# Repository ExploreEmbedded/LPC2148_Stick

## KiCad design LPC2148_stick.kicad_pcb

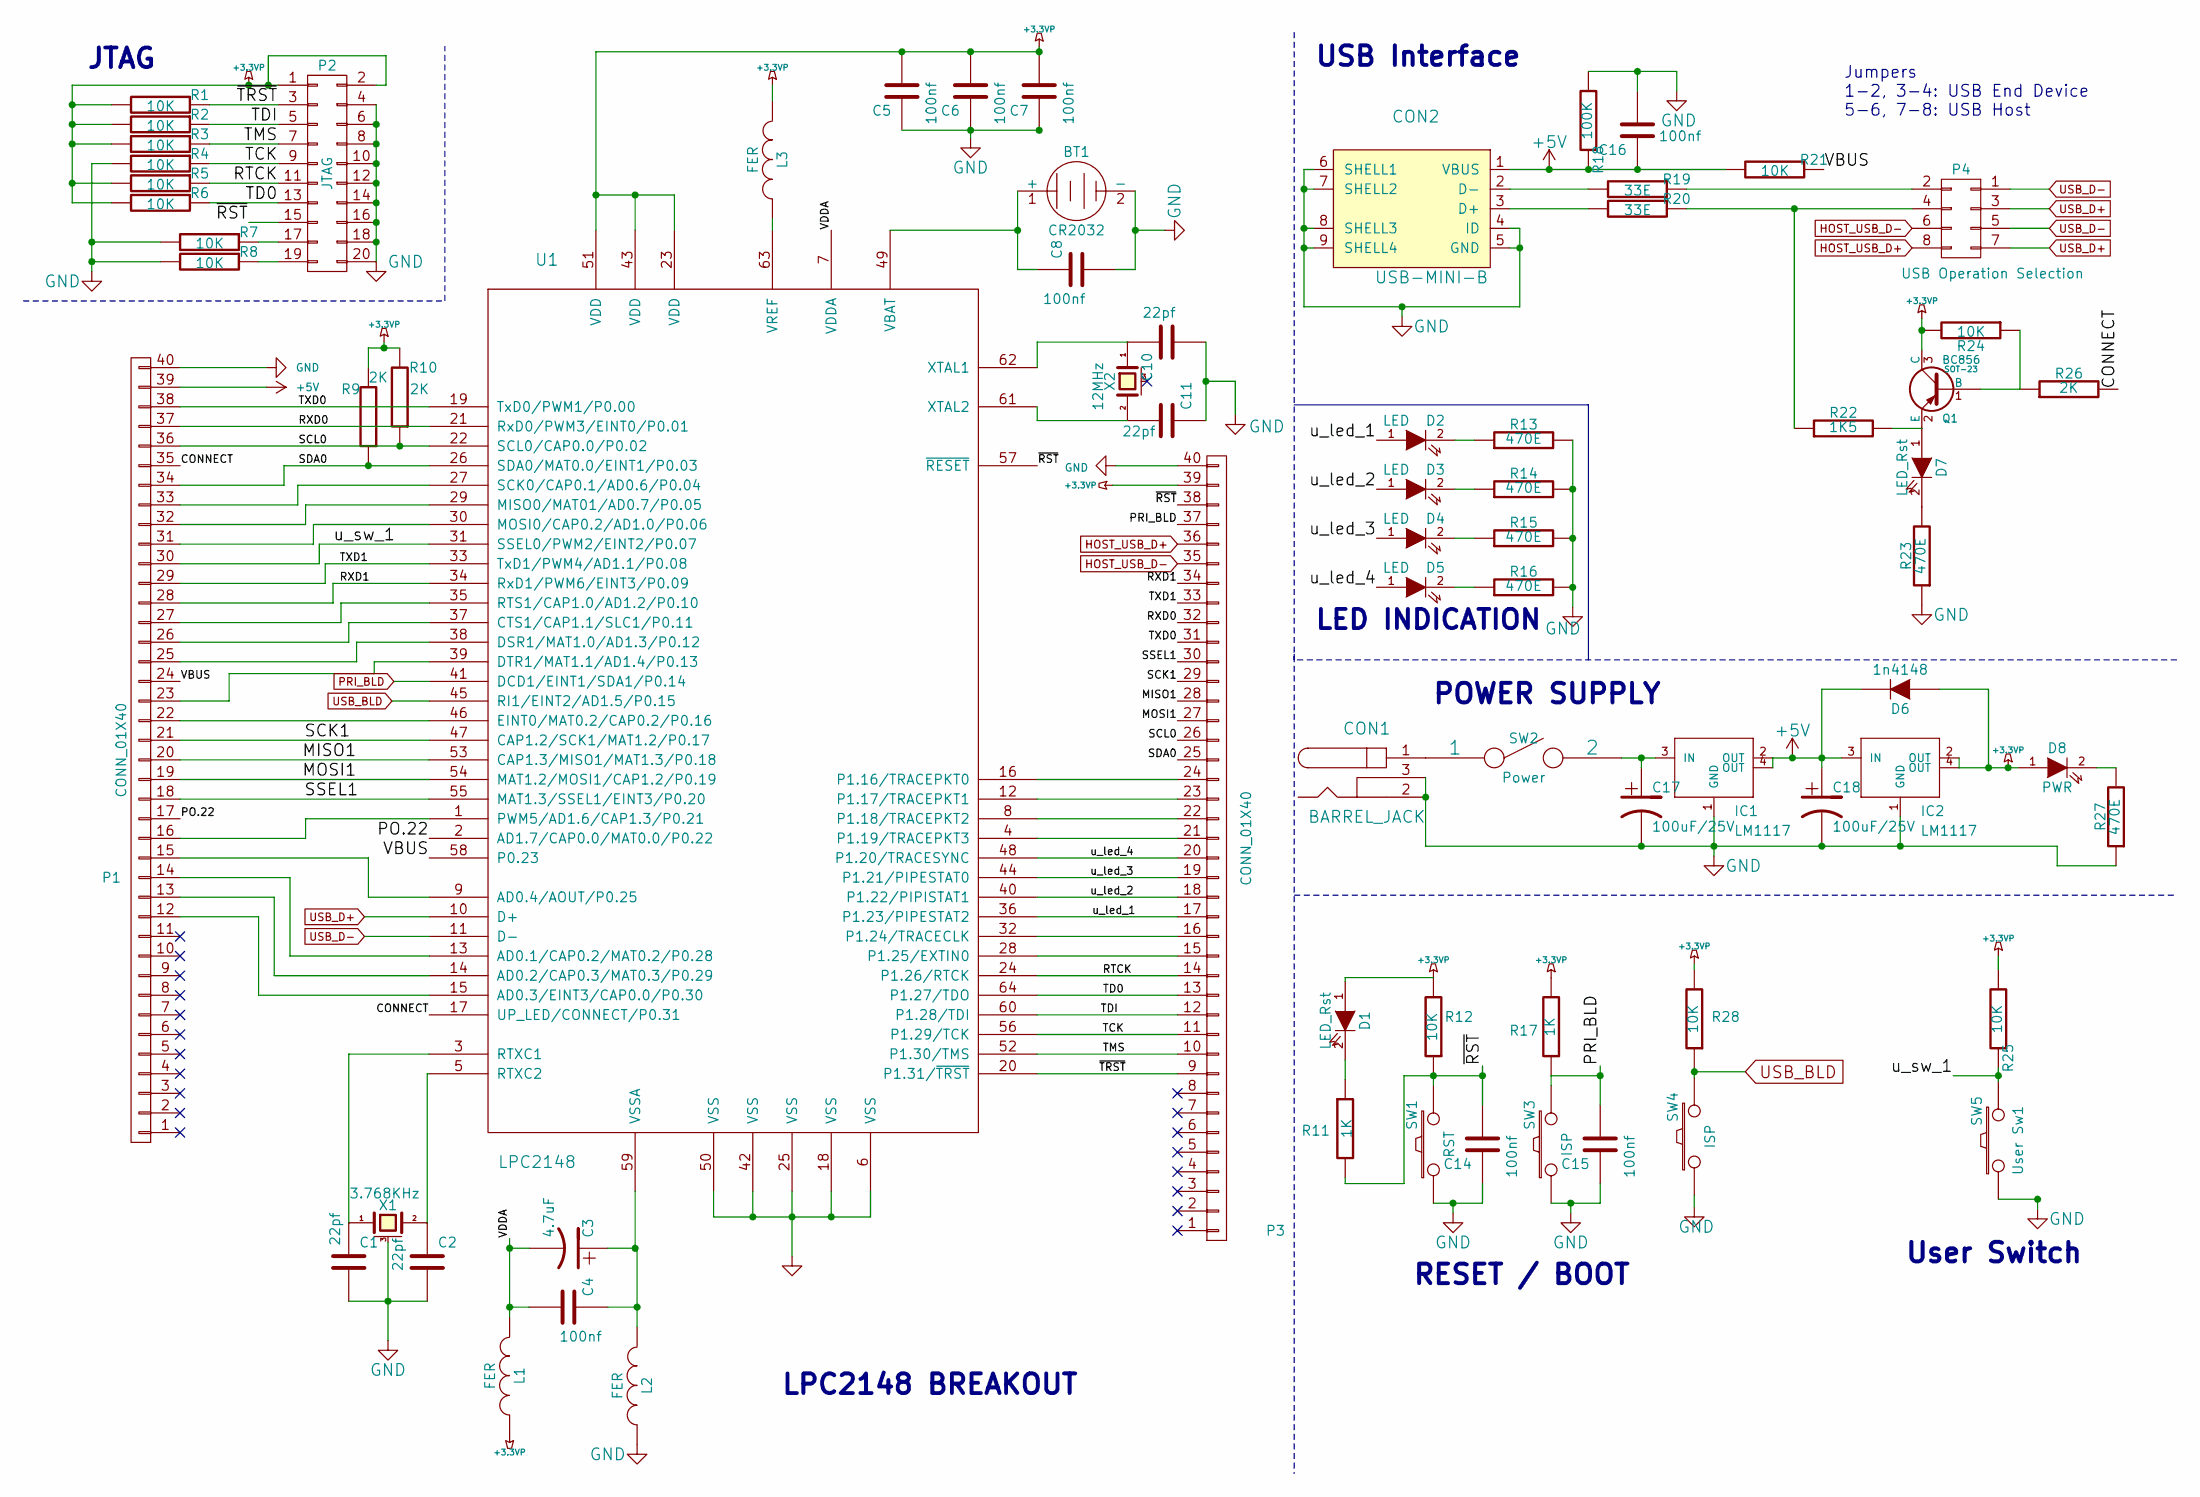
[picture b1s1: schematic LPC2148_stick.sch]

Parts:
BT1: CR2032
C1, C2, C10, C11: 22pf
C3: 4.7uF
C4, C5, C6, C7, C8, C14, C15, C16: 100nf
C17, C18: 100uF/25V
CON1: BARREL_JACK
CON2: USB-MINI-B
D1, D7: LED_Rst
D2, D3, D4, D5: LED
D6: 1n4148
D8: PWR
IC1, IC2: LM1117
L1, L2, L3: FER
P1, P3: CONN_01X40
P2: JTAG
P4: USB Operation Selection
Q1: BC856; SOT-23
R1, R2, R3, R4, R5, R6, R7, R8, R12, R21, R24, R25, R28: 10K
R9, R10, R26: 2K
R11, R17: 1K
R13, R14, R15, R16, R23, R27: 470E
R18: 100K
R19, R20: 33E
R22: 1K5
SW1: RST
SW2: Power
SW3, SW4: ISP
SW5: User Sw1
U1: LPC2148
X1: 3.768KHz
X2: 12MHz

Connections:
+3.3VP: C5.2, C6.2, C7.2, D1.1 (A), D6.1 (A), D8.1 (A), IC2.2 (OUT), IC2.4 (OUT), L1.2, L3.1, P2.1, P2.2, P3.39, Q1.3 (C), R1.2, R2.2, R3.2, R5.2, R6.2, R9.2, R10.2, R12.2, R17.2, R24.2, R25.2, R28.2, U1.23 (VDD), U1.43 (VDD), U1.51 (VDD)
+5V: C16.1, C18.1, CON2.1 (VBUS), D6.2 (K), IC1.2 (OUT), IC1.4 (OUT), IC2.3 (IN), P1.39, R18.1, R21.2
/CONNECT: P1.35, R26.2, U1.17 (UP_LED/CONNECT/P0.31)
/MISO1: P1.20, P3.28, U1.53 (CAP1.3/MISO1/MAT1.3/P0.18)
/MOSI1: P1.19, P3.27, U1.54 (MAT1.2/MOSI1/CAP1.2/P0.19)
/RTCK: P2.11, P3.14, R5.1, U1.24 (P1.26/RTCK)
/RXD0: P1.37, P3.32, U1.21 (RxD0/PWM3/EINT0/P0.01)
/RXD1: P1.28, P3.34, U1.34 (RxD1/PWM6/EINT3/P0.09)
/SCK1: P1.21, P3.29, U1.47 (CAP1.2/SCK1/MAT1.2/P0.17)
/SCL0: P1.36, P3.26, R10.1, U1.22 (SCL0/CAP0.0/P0.02)
/SDA0: P1.34, P3.25, R9.1, U1.26 (SDA0/MAT0.0/EINT1/P0.03)
/SSEL1: P1.18, P3.30, U1.55 (MAT1.3/SSEL1/EINT3/P0.20)
/TCK: P2.9, P3.11, R4.1, U1.56 (P1.29/TCK)
/TD0: P2.13, P3.13, R6.1, U1.64 (P1.27/TDO)
/TDI: P2.5, P3.12, R2.1, U1.60 (P1.28/TDI)
/TMS: P2.7, P3.10, R3.1, U1.52 (P1.30/TMS)
/TXD0: P1.38, P3.31, U1.19 (TxD0/PWM1/P0.00)
/TXD1: P1.29, P3.33, U1.33 (TxD1/PWM4/AD1.1/P0.08)
/VBUS: P1.24, R21.1, U1.58 (P0.23)
/VDDA: C3.2, C4.2, L1.1, U1.7 (VDDA)
/u_led_1: D2.1 (A), P3.17, U1.36 (P1.23/PIPESTAT2)
/u_led_2: D3.1 (A), P3.18, U1.40 (P1.22/PIPISTAT1)
/u_led_3: D4.1 (A), P3.19, U1.44 (P1.21/PIPESTAT0)
/u_led_4: D5.1 (A), P3.20, U1.48 (P1.20/TRACESYNC)
/u_sw_1: P1.30, R25.1, SW5.2, U1.31 (SSEL0/PWM2/EINT2/P0.07)
/~RST: C14.2, P2.15, P3.38, R11.2, R12.1, SW1.2, U1.57 (~RESET)
/~TRST: P2.3, P3.9, R1.1, U1.20 (P1.31/~TRST)
GND: BT1.2 (-), C1.2, C2.2, C5.1, C6.1, C7.1, C8.2, C10.2, C11.1, C14.1, C15.1, C16.2, C17.2, C18.2, CON1.2, CON1.3, CON2.4 (ID), CON2.5 (GND), CON2.6 (SHELL1), CON2.7 (SHELL2), CON2.8 (SHELL3), CON2.9 (SHELL4), IC1.1 (GND), IC2.1 (GND), L2.2, P1.40, P2.4, P2.6, P2.8, P2.10, P2.12, P2.14, P2.16, P2.18, P2.20, P3.40, R4.2, R7.2, R8.2, R13.2, R14.2, R15.2, R16.2, R18.2, R23.1, R27.1, SW1.1, SW3.1, SW4.1, SW5.1, U1.6 (VSS), U1.18 (VSS), U1.25 (VSS), U1.42 (VSS), U1.50 (VSS), X1.3 (case)
HOST_USB_D+: P3.36, P4.8
HOST_USB_D-: P3.35, P4.6
unnamed: BT1.1 (+), C8.1, U1.49 (VBAT)
unnamed: C1.1, U1.3 (RTXC1), X1.1
unnamed: C2.1, U1.5 (RTXC2), X1.2
unnamed: C3.1, C4.1, L2.1, U1.59 (VSSA)
unnamed: C10.1, U1.62 (XTAL1), X2.1
unnamed: C11.2, U1.61 (XTAL2), X2.2
unnamed: C17.1, IC1.3 (IN), SW2.2
unnamed: CON1.1, SW2.1
unnamed: CON2.2 (D-), R19.2
unnamed: CON2.3 (D+), R20.2
unnamed: D1.2 (K), R11.1
unnamed: D2.2 (K), R13.1
unnamed: D3.2 (K), R14.1
unnamed: D4.2 (K), R15.1
unnamed: D5.2 (K), R16.1
unnamed: D7.1 (A), Q1.2 (E), R22.2
unnamed: D7.2 (K), R23.2
unnamed: D8.2 (K), R27.2
unnamed: L3.2, U1.63 (VREF)
unnamed: P1.12, U1.15 (AD0.3/EINT3/CAP0.0/P0.30)
unnamed: P1.13, U1.14 (AD0.2/CAP0.3/MAT0.3/P0.29)
unnamed: P1.14, U1.13 (AD0.1/CAP0.2/MAT0.2/P0.28)
unnamed: P1.15, U1.9 (AD0.4/AOUT/P0.25)
unnamed: P1.22, U1.46 (EINT0/MAT0.2/CAP0.2/P0.16)
unnamed: P1.23, U1.39 (DTR1/MAT1.1/AD1.4/P0.13)
unnamed: P1.25, U1.38 (DSR1/MAT1.0/AD1.3/P0.12)
unnamed: P1.26, U1.37 (CTS1/CAP1.1/SLC1/P0.11)
unnamed: P1.27, U1.35 (RTS1/CAP1.0/AD1.2/P0.10)
unnamed: P1.31, U1.30 (MOSI0/CAP0.2/AD1.0/P0.06)
unnamed: P1.32, U1.29 (MISO0/MAT01/AD0.7/P0.05)
unnamed: P1.33, U1.27 (SCK0/CAP0.1/AD0.6/P0.04)
unnamed: P2.17, R7.1
unnamed: P2.19, R8.1
unnamed: P3.15, U1.28 (P1.25/EXTIN0)
unnamed: P3.16, U1.32 (P1.24/TRACECLK)
unnamed: P3.21, U1.4 (P1.19/TRACEPKT3)
unnamed: P3.22, U1.8 (P1.18/TRACEPKT2)
unnamed: P3.23, U1.12 (P1.17/TRACEPKT1)
unnamed: P3.24, U1.16 (P1.16/TRACEPKT0)
unnamed: P4.2, R19.1
unnamed: P4.4, R20.1, R22.1
unnamed: Q1.1 (B), R24.1, R26.1
PRI_BLD: C15.2, P3.37, R17.1, SW3.2, U1.41 (DCD1/EINT1/SDA1/P0.14)
USB_BLD: R28.1, SW4.2, U1.45 (RI1/EINT2/AD1.5/P0.15)
USB_D+: P4.3, P4.7, U1.10 (D+)
USB_D-: P4.1, P4.5, U1.11 (D-)

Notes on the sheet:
Jumpers 1-2, 3-4: USB End Device 5-6, 7-8: USB Host
JTAG
RESET / BOOT
LPC2148 BREAKOUT
USB Interface
POWER SUPPLY
User Switch
LED INDICATION

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
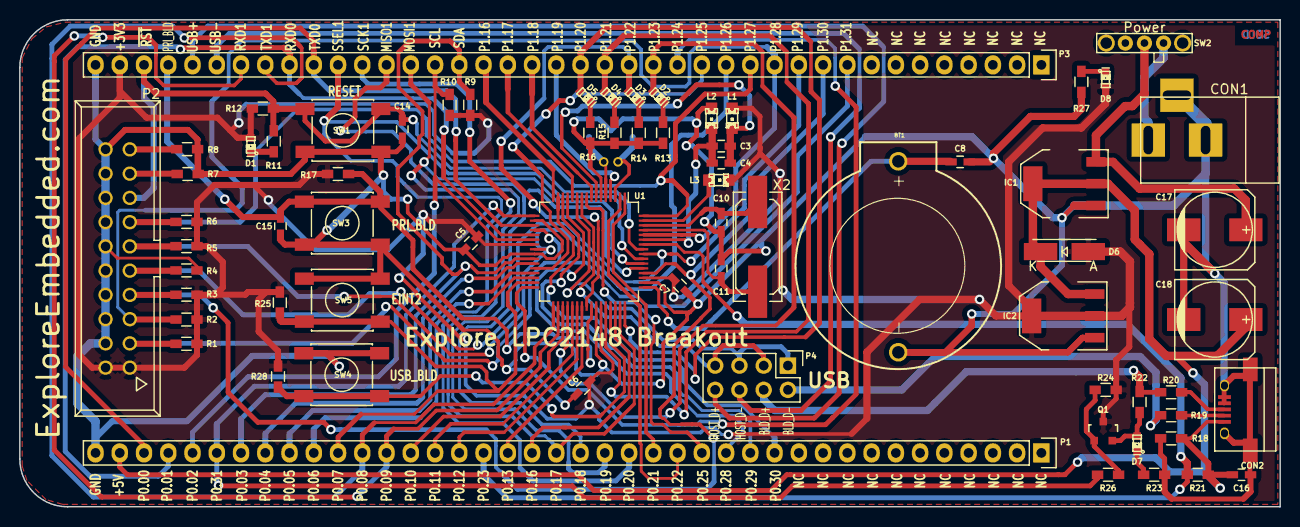
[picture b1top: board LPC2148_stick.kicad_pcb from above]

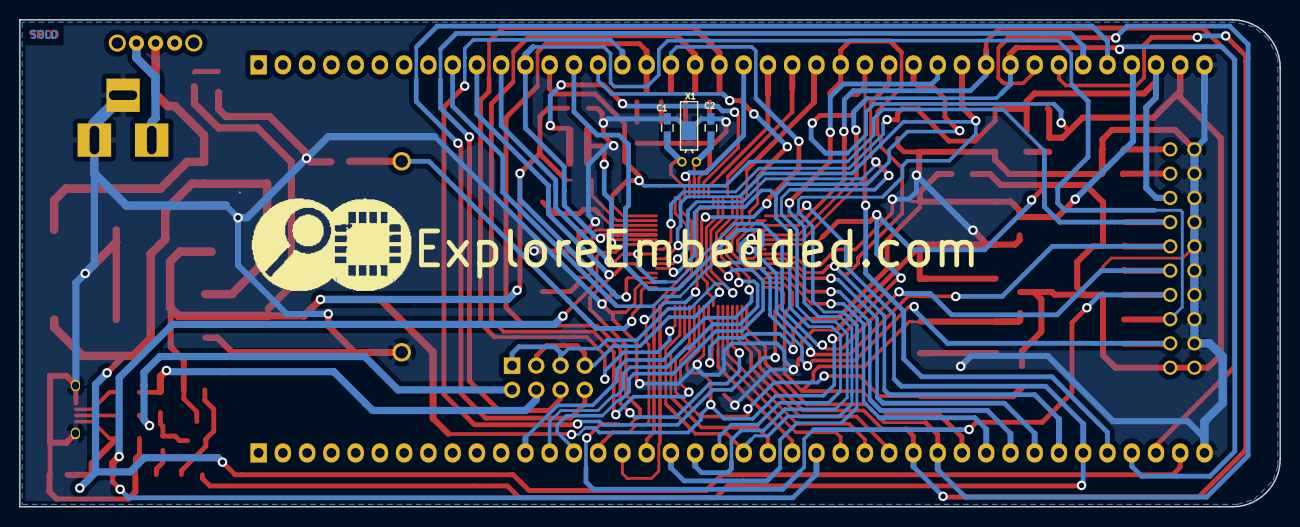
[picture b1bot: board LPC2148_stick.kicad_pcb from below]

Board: 2 copper layers, 132.0 x 51.0 mm, 73 parts (4 on the bottom side), 78 nets.

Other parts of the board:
EE_LOGO: EE_LOGO(2)

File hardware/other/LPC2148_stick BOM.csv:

Id,Designator,Package,Designation
1,X1,Crystal_Round_Horizontal_2mm_NEW,3.768KHz
2,BT1,BATT_rtc_XL,CR2032
3,"C1,C2,C10,C11",C_0603_HandSoldering,22pf
4,C3,C_0603_HandSoldering,4.7uF
5,"C4,C5,C6,C7,C8,C14,C15,C16",C_0603_HandSoldering,100nf
6,"C17,C18",c_elec_8x10.5,100uF/25V
7,CON1,BARREL_JACK,BARREL_JACK
8,"IC1,IC2",SOT-223,LM1117
9,"L1,L2,L3",LED-0805,FER
10,"P1,P3",Pin_Header_Straight_1x40,CONN_01X40
11,P2,VASCH10x2,JTAG
12,P4,Pin_Header_Straight_2x04,USB Operation Selection
13,Q1,SOT-23,BC856
14,"R1,R2,R3,R4,R5,R6,R7,R8,R12,R21,R24,R25,R28",R_0603_HandSoldering,10K
15,"R9,R10,R26",R_0603_HandSoldering,2K
16,"R11,R17",R_0603_HandSoldering,1K
17,"R13,R14,R15,R16,R23,R27",R_0603_HandSoldering,470E
18,R18,R_0603_HandSoldering,100K
19,"R19,R20",R_0603_HandSoldering,33E
20,R22,R_0603_HandSoldering,1K5
21,U1,LQFP-64_10x10mm_Pitch0.5mm,LPC2148
22,X2,Q_49U3HMS,12MHz
23,SW1,SW_PUSH_SMALL_smd_NEW,RST
24,"SW3,SW4",SW_PUSH_SMALL_smd_NEW,ISP
25,SW5,SW_PUSH_SMALL_smd_NEW,User Sw1
26,D6,ZenerDiode_SMD,1n4148
27,"D1,D7",LED-0603_NEW,LED_Rst
28,"D2,D3,D4,D5",LED-0603_NEW,LED
29,D8,LED-0603_NEW,PWR
30,SW2,Micro_slide_switch-spst_2mm_new,Power
31,CON2,USB_Micro-B_SMD,USB-MINI-B
32,EE_LOGO,EE_LOGO(2),
,,,
,,,

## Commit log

2015-06-29 added design files
2015-07-03 added final designs
2015-07-03 CORRECTED FILES
2015-07-03 new files
2015-07-06 added files with logo
2015-07-06 changed usb
2015-07-06 final
2015-07-06 logo and micro switch ffotprint
2015-07-25 Legend modified
2015-08-11 fritzing
2015-08-25 Sample codes
    updated folder structure as well, tested sample codes with USB
    bootloader
2015-08-25 folder structure change
2015-08-26 sample code updated
2016-07-21 Added Keil sample codes
    Added Keil sample codes
2016-07-25 Added Keil Examples
    Added Keil Examples
2017-04-10 Added GLCD library
    Added GLCD library
2017-04-10 Remapped the GLCD pins
    Remapped the GLCD pins
2019-01-01 created hello1.txt
